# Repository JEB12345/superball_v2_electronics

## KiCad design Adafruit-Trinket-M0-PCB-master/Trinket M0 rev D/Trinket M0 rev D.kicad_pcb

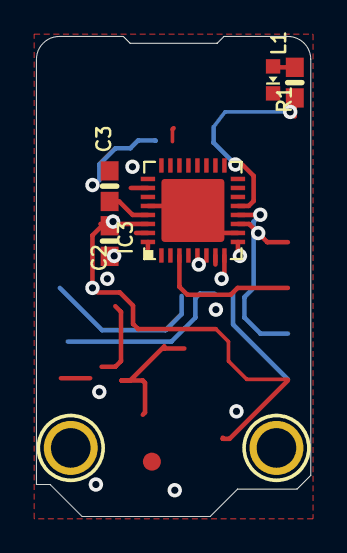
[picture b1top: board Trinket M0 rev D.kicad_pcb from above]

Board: 16 copper layers, 15.2 x 26.7 mm, 10 parts (0 on the bottom side), 7 nets.

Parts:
C2, C3: 1uF; 0603-NO
IC3: ATSAMD21E; QFN32_5MM
L1: red; CHIPLED_0603_NOOUTLINE
R1: 1.5K; 0603-NO
SWC1: TPB1,27; B1,27
SWD1: TPB1,27; B1,27
U$6: FIDUCIAL_1MM
U$8, U$9: MOUNTINGHOLE2.0; MOUNTINGHOLE_2.0_PLATED

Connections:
3.3V: C2.1, IC3.9, IC3.30
GND: C2.2, C3.2, IC3.10, IC3.28, IC3.33, L1.C
unnamed: C3.1, IC3.29
unnamed: IC3.13, R1.2
unnamed: IC3.31, SWC1.TP
unnamed: IC3.32, SWD1.TP
unnamed: L1.A, R1.1

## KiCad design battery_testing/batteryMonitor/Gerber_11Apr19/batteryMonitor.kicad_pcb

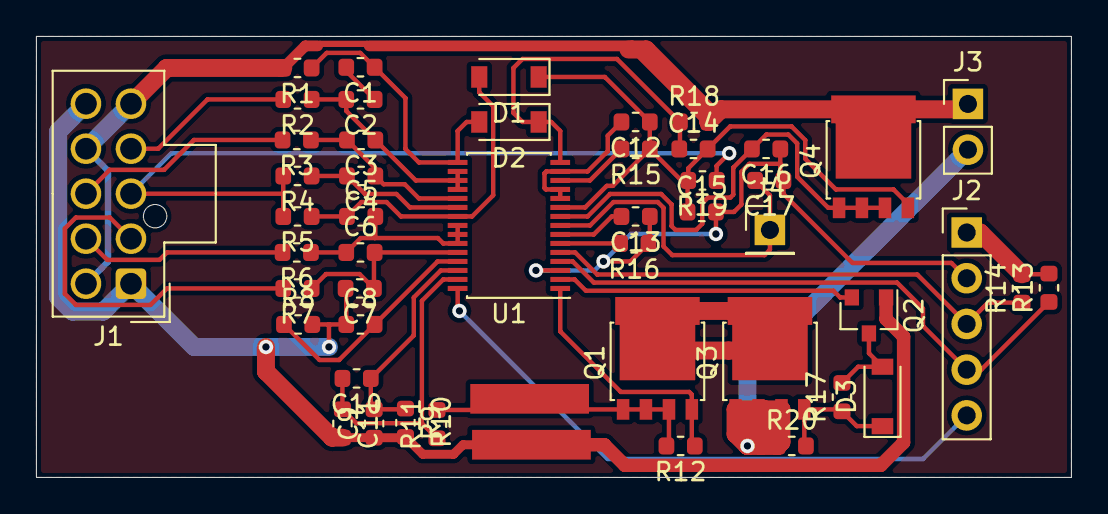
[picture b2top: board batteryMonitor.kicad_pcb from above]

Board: 2 copper layers, 57.5 x 24.5 mm, 49 parts (0 on the bottom side), 38 nets.

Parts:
C1, C2, C3, C4, C5, C6, C7, C8, C12, C13, C16: 1uF; C_0603_1608Metric
C9, C10, C11: 0.1Uf; C_0603_1608Metric
C14, C15: 10uF; C_0603_1608Metric
C17: 4.7uF; C_0603_1608Metric
D1, D2, D3: MMSD914; D_SOD-123
J1: Battery Input Connector; Molex_Nano-Fit_105310-xx10_2x05_P2.50mm_Vertical
J2: Conn_01x05_Male; PinHeader_1x05_P2.54mm_Vertical
J3: Conn_01x02_Female; PinHeader_1x02_P2.54mm_Vertical
J4: Conn_01x01_Female; PinHeader_1x01_P2.54mm_Vertical
Q1, Q3, Q4: PSMN5R8-40YS; LFPAK56
Q2: IRLML6402; SOT-23
R1, R2, R3, R4, R5, R6, R7, R8, R13, R14: 1k; R_0603_1608Metric
R9, R11, R18, R19: 100; R_0603_1608Metric
R10: 0.009; LONG_2512
R12, R17, R20: 1M; R_0603_1608Metric
R15, R16: 10k; R_0603_1608Metric
U1: BQ76930; TSSOP-30_4.4x7.8mm_P0.5mm

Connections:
/A: J1.3, R4.2, R5.2, R19.1
/Batt_GND: C7.2, C8.1, C9.1, C11.2, J1.1, J1.10, Q2.1, R8.2, R9.2, R10.1
/P1: J1.2, R7.2
/P2: J1.7, R6.2
/P4: J1.8, R3.2
/P5: J1.4, R2.2
/Pack+: J1.5, J1.6, J1.9, J3.1, Q4.5, R1.2, R18.2
/Pack-: J3.2, Q3.1, Q3.2, Q3.3, R20.1
/REGOUT: C17.2, J4.1, U1.8
/REGSRC: C16.2, Q4.1, Q4.2, Q4.3, U1.9
/Top_Batt: C14.1, D2.1, R18.1, U1.15
/VC5: C5.1, D1.2, R5.1, U1.22
/VC5x: C12.1, C14.2, C15.1, D1.1, Q4.4, R15.1, R19.2, U1.10
/alert: J2.5, U1.30
/batt_monitor_SCL: J2.3, R14.1, U1.5
/batt_monitor_SDA: J2.4, R13.1, U1.4
/external_3v3: J2.1, R13.2, R14.2
/low_GND: C13.1, C15.2, C16.1, C17.1, J2.2, R16.1, U1.3
unnamed: C1.1, D2.2, R1.1, U1.16
unnamed: C1.2, C2.1
unnamed: C2.2, C3.1, R2.1, U1.17, U1.18, U1.19
unnamed: C3.2, C4.1, R3.1, U1.20
unnamed: C4.2, R4.1, U1.21
unnamed: C5.2, C6.1, R6.1, U1.23, U1.24, U1.25
unnamed: C6.2, C7.1, R7.1, U1.26
unnamed: C8.2, R8.1, U1.27
unnamed: C9.2, C10.1, R9.1, U1.28
unnamed: C10.2, C11.1, R11.1, U1.29
unnamed: C12.2, U1.11, U1.12, U1.14
unnamed: C13.2, U1.7
unnamed: D3.1, Q3.4, R17.1, R20.2
unnamed: D3.2, Q2.3, R17.2
unnamed: Q1.1, Q1.2, Q1.3, R10.2, R11.2, R12.2
unnamed: Q1.4, R12.1, U1.1
unnamed: Q1.5, Q3.5
unnamed: Q2.2, U1.2
unnamed: R15.2, U1.13
unnamed: R16.2, U1.6

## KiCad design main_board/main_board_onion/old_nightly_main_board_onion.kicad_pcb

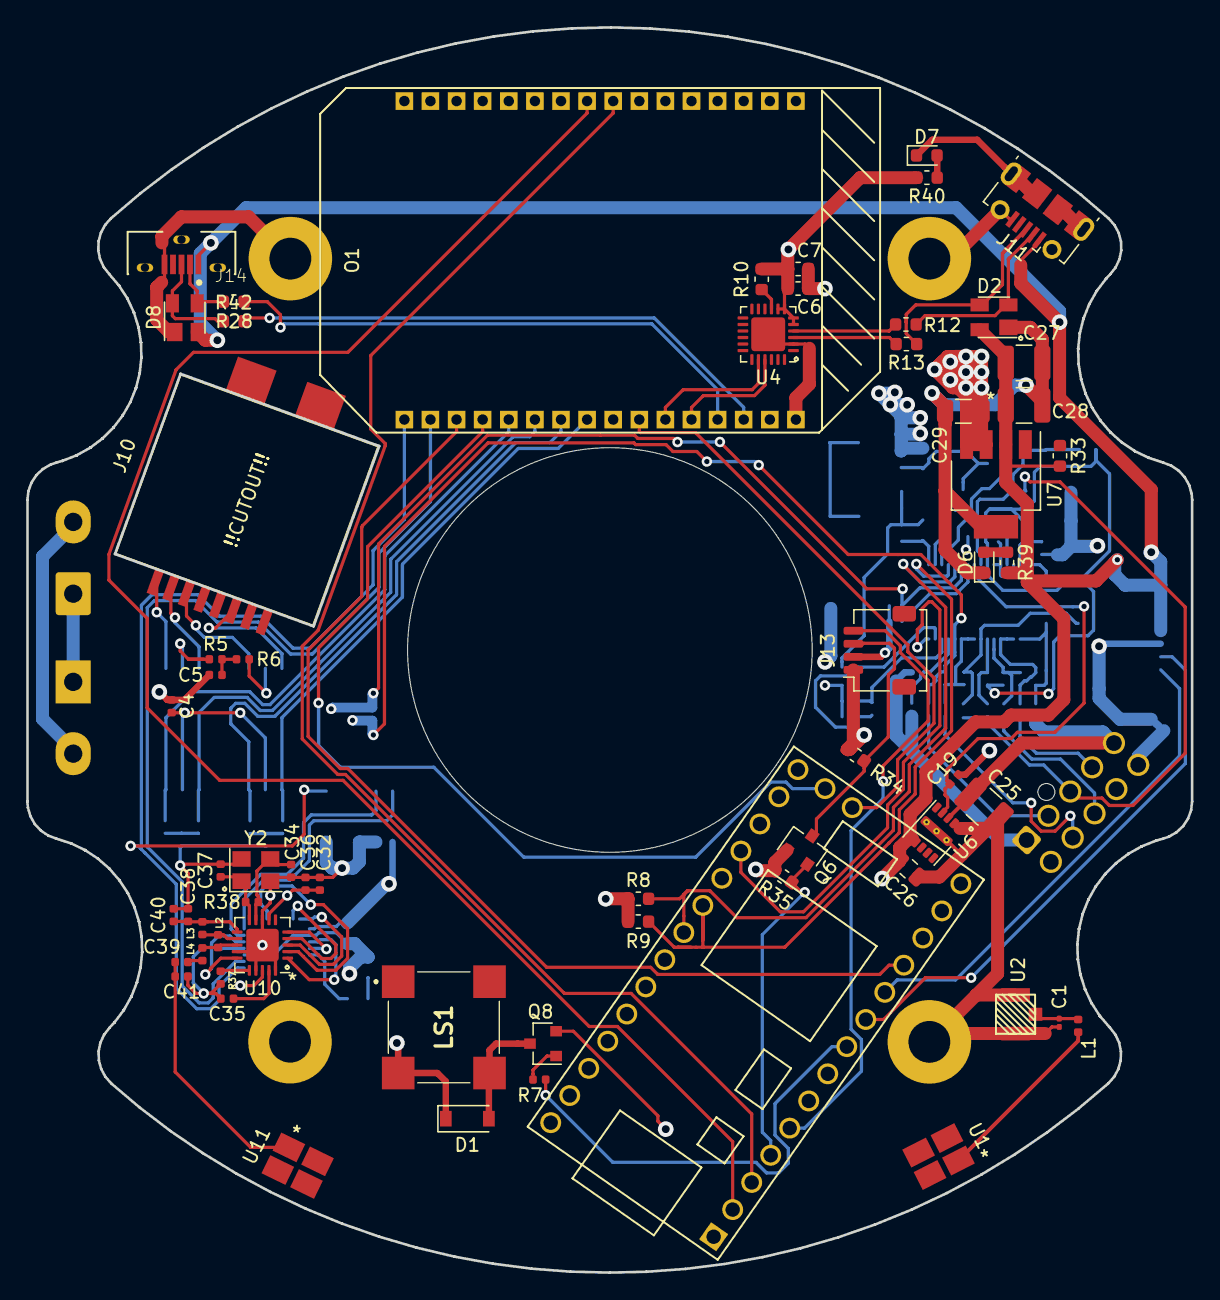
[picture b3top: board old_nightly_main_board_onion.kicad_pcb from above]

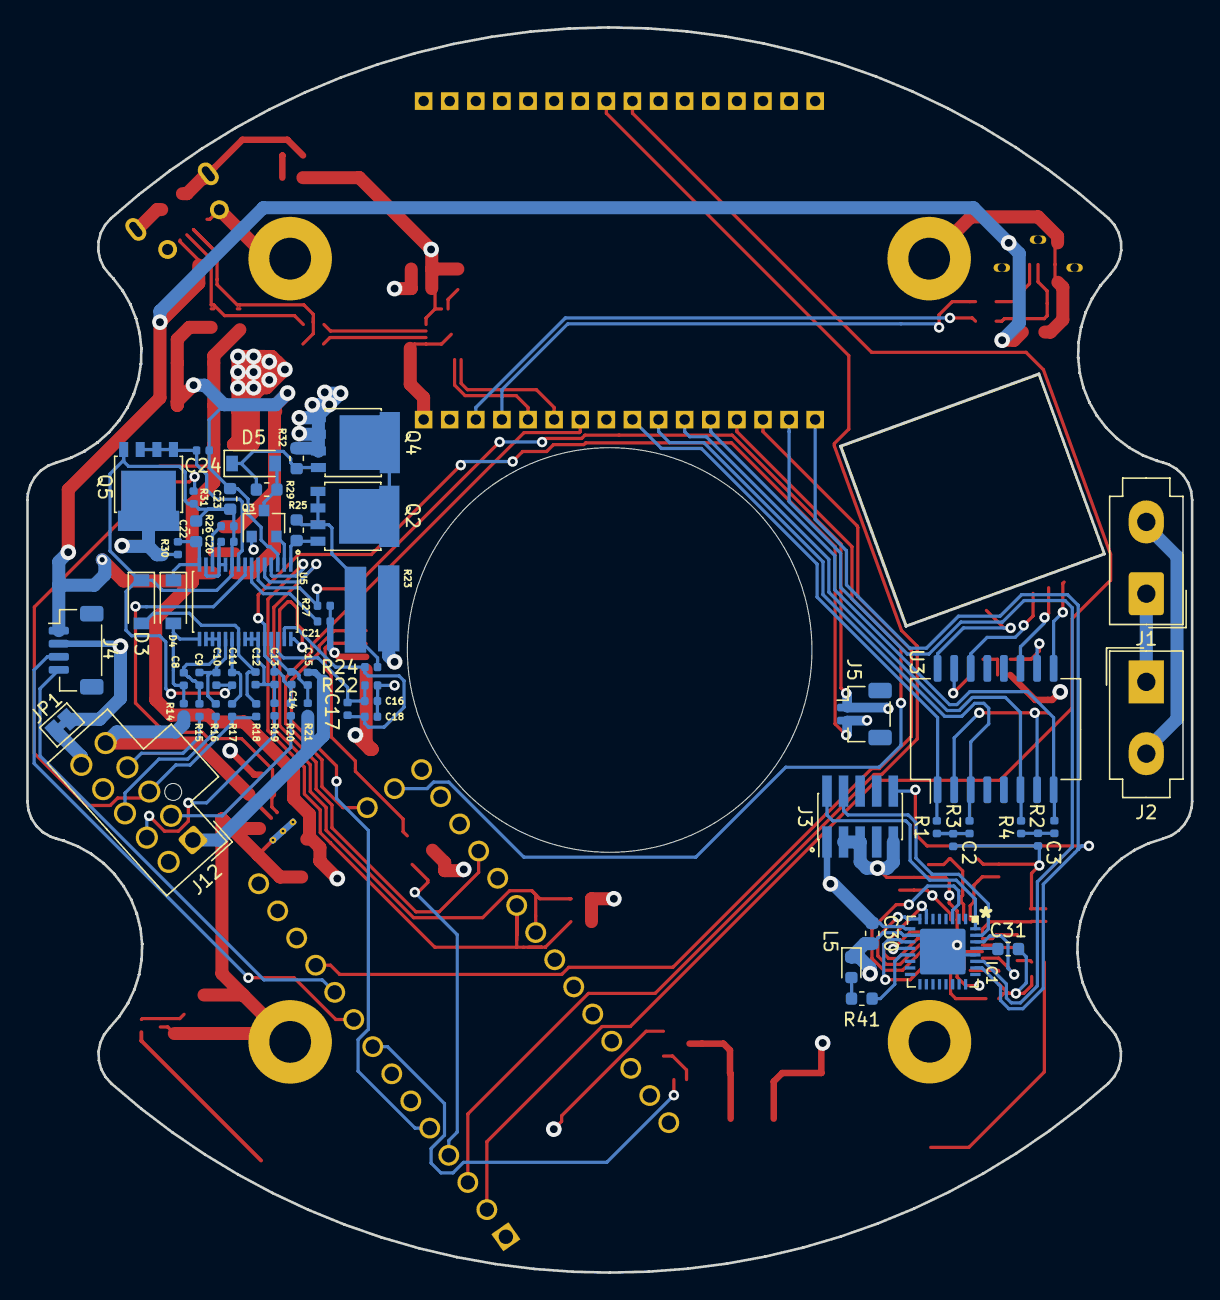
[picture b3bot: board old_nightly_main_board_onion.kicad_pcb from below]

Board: 4 copper layers, 89.2 x 95.4 mm, 128 parts (61 on the bottom side), 102 nets.

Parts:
C1: 1.3pF; C_0201_0603Metric
C2, C3: 100nF; C_0402_1005Metric
C4, C8, C9, C10, C11, C12, C13, C14, C15, C20, C21, C24: 1uF; C_0402_1005Metric
C5: 1nF/2KV; C_0402_1005Metric
C6: 0.1uF; C_0603_1608Metric
C7: 4.7uF; C_0603_1608Metric
C16, C17, C18: 0.1Uf; C_0402_1005Metric
C19: 4.7uF; C_0402_1005Metric
C22, C23: 10uF; C_0603_1608Metric
C25: C3225X7R1H106M250AC; R_1210_3225Metric
C26: 22uF; C_0805_2012Metric
C27, C28: C1210C476M9RACTU; C_1210_3225Metric
C29: TAJA336K006RNJ; C_1206_3216Metric
C30, C31: 1uF; C_0603_1608Metric
C32: 10nF; C_0402_1005Metric
C34: 1nF; C_0402_1005Metric
C35: 33nF; C_0402_1005Metric
C36, C37: 12pF; C_0402_1005Metric
C38: 2.2nF; C_0402_1005Metric
C39: 1.5pF; C_0402_1005Metric
C40: 4.7pF; C_0402_1005Metric
C41: 1.0pF; C_0402_1005Metric
D1: BAT42W-V; D_SOD-123
D2, D8: SP0503BAHT; SOT-143
D3, D4, D5: MMSD914; D_SOD-123
D6: Green; LED_0603_1608Metric
D7: Red; LED_0603_1608Metric
IC1: ATSAMD21E; QFN32_5MM
J1, J2: Hebi_Power; Molex_Mini-Fit_Jr_5566-02A_2x01_P4.20mm_Vertical
J3: Conn_02x05_Odd_Even; PinHeader_2x05_P1.27mm_Vertical_SMD
J4: SensorBoard; Molex_Pico-Clasp_501331-0407_1x04-1MP_P1.00mm_Vertical
J5: Power_On_Switch; Molex_Pico-Clasp_501331-0207_1x02-1MP_P1.00mm_Vertical
J6, J7, J8, J9: Mounting_Hole; MountingHole_3.2mm_M3_Pad
J10: RJ45; 1-338088-3
J11: USB_B_Micro_Omega; USB_Micro-B_Molex-105017-0001
J12: Battery Input Connector; Molex_Nano-Fit_105310-xx10_2x05_P2.50mm_Vertical
J13: LED_Pressure; Molex_Pico-Clasp_202396-0407_1x04-1MP_P1.00mm_Horizontal
J14: USB_B_Micro; MOLEX_105133-0001_0
JP1: SolderJumper_2_Bridged; SolderJumper-2_P1.3mm_Bridged_Pad1.0x1.5mm
L1: 1.8nH; R_0402_1005Metric
L2: 8.2nH; L_0402_1005Metric
L3: 2.7nH; L_0402_1005Metric
L4: 3.9nH; L_0402_1005Metric
L5: red; LED_0603_1608Metric
LS1: CMT-8530S-SMT-TR; CMT8530SSMTTR
O1: Omega2; Omega2p
Q2, Q4, Q5: PSMN5R8-40YS; LFPAK56
Q3: IRLML6402; SOT-23
Q6: BSS138; SOT-23
Q8: MMBT3904; SOT-23
R1, R2, R3, R4: 49.9; R_0402_1005Metric
R5, R6: 75; R_0402_1005Metric
R7, R22, R24, R30, R31: 100; R_0402_1005Metric
R8, R9, R33: 10k; R_0603_1608Metric
R10, R39, R40, R41: 1k; R_0603_1608Metric
R12, R13, R28, R42: 33; R_0603_1608Metric
R14, R15, R16, R17, R18, R19, R20, R21: 1k; R_0402_1005Metric
R23: 0.009; LONG_2512
R25, R29, R32: 1M; R_0603_1608Metric
R26, R27: 10k; R_0402_1005Metric
R34, R35: 10K; R_0603_1608Metric
R37: 22k; R_0402_1005Metric
R38: 1M; R_0402_1005Metric
U1, U11: molex_antenna_47948-0001; Molex_47948-0001
U2: conn_smt; U.FL-R-SMT-1(01)
U3: H1102; SOIC-16W_7.5x12.8mm_P1.27mm
U4: CP2102N-A01-GQFN24; QFN-24-1EP_4x4mm_P0.5mm_EP2.6x2.6mm
U5: BQ76930; TSSOP-30_4.4x7.8mm_P0.5mm
U6: LMZM23601V5; Texas_SIL0010A_MicroSiP-10-1EP_3.8x3mm_P0.6mm_EP0.7x2.9mm_T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
U7: lp3965v3; SOT-223-5
U8: Teensy-LC; Teensy_LC_Min
U10: nRF24L01P; QFN-20-1EP_4x4mm_P0.5mm_EP2.5x2.5mm
Y2: CX3225SB16000H0FLJCC; Crystal_SMD_3225-4Pin_3.2x2.5mm

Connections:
+3V3: C6.1, C7.1, C29.1, C30.1, C32.1, C34.1, D1.1, IC1.9, IC1.30, J3.1, LS1.2, O1.B2, Q6.1, R8.1, R9.1, R10.1, R35.1, R40.2, U4.5, U4.6, U4.7, U4.8, U7.3, U7.4, U10.7, U10.15, U10.18
+5V: C26.2, C27.1, C28.1, D2.4, D8.2, J4.1, J11.1, J13.1, J14.1, R33.2, R34.1, R39.2, U6.6, U6.7, U7.2, U8.33
/Button_L: J5.1, R27.2, U5.6
/Button_R: C13.2, C14.1, J5.2, R20.1, U5.26
/I2C_SCL: R8.2, U5.5, U8.26
/I2C_SDA: R9.2, U5.4, U8.25
/LED_Strip_CMD: J13.3, Q6.3, R34.2
/Omega2/D+IN_Omega: D2.3, J11.3, R13.1
/Omega2/D+_Omega: R13.2, U4.3
/Omega2/D-IN_Omega: D2.2, J11.2, R12.1
/Omega2/D-_Omega: R12.2, U4.4
/Omega2/PC_RXD: O1.B6, U4.20
/Omega2/PC_TXD: O1.B5, U4.21
/Omega2/RX+: O1.B12, R2.2, U3.8
/Omega2/RX-: O1.B11, R4.2, U3.6
/Omega2/TX+: O1.B10, R3.2, U3.3
/Omega2/TX-: O1.B9, R1.2, U3.1
/Omega2/extra_USB+: O1.B3, R42.2
/Omega2/extra_USB-: O1.B4, R28.2
/Omega2/extra_in_USB+: D8.4, J14.3, R42.1
/Omega2/extra_in_USB-: D8.3, J14.2, R28.1
/Operational_Sig: IC1.27, O1.B15
/Pack+: C25.1, J1.2, J2.2, J12.5, J12.6, J12.9, Q5.5, R14.2, R30.2, U6.3
/Pack_GND: J1.1, J2.1, Q4.1, Q4.2, Q4.3, R32.1
/Pressure_Sensor: J13.4, U8.5
/REGOUT: C19.2, U5.8, U6.4
/SensorBoard_RX: J4.3, U8.9
/SensorBoard_TX: J4.4, U8.10
/Teensy/LED_Strip_Lighting: Q6.2, R35.2, U8.4
/Teensy/buzzer: R7.2, U8.8
/Teensy_Program: O1.B7, U8.18
/Teensy_RX: O1.A9, U8.2
/Teensy_Ready: O1.B14, U8.11
/Teensy_TX: O1.A8, U8.3
/batteryMonitor/A: J12.3, R17.2, R18.2, R31.1
/batteryMonitor/Batt_GND: C15.2, C16.1, C18.2, J12.1, J12.10, JP1.1, Q3.1, R21.2, R22.2, R23.1
/batteryMonitor/P1: J12.2, R20.2
/batteryMonitor/P2: J12.7, R19.2
/batteryMonitor/P4: J12.8, R16.2
/batteryMonitor/P5: J12.4, R15.2
/batteryMonitor/REGSRC: C24.2, Q5.1, Q5.2, Q5.3, U5.9
/batteryMonitor/Top_Batt: C22.1, D4.1, R30.1, U5.15
/batteryMonitor/VC5: C12.1, D3.2, R18.1, U5.22
/batteryMonitor/VC5x: C10.2, C11.1, C20.1, C22.2, C23.1, D3.1, Q5.4, R26.1, R31.2, U5.10
/bq76930_Alert: U5.30, U8.23
/mRF_MOSI: IC1.7, U10.4
/nRF24L01+Trinket/Trinket_M0_rev_D/SWCLK: IC1.31, J3.4
/nRF24L01+Trinket/Trinket_M0_rev_D/SWDIO: IC1.32, J3.2
/nRF_CE: IC1.11, U10.1
/nRF_CSN: IC1.3, U10.2
/nRF_MISO: IC1.12, U10.5
/nRF_SCK: IC1.8, U10.3
/~M0_RESET: IC1.26, J3.10, O1.B16
/~Reset_Teensy: O1.B13, U8.19
GND: C1.2, C2.2, C3.2, C4.1, C5.1, C6.2, C7.2, C19.1, C21.1, C23.2, C24.1, C25.2, C26.1, C27.2, C28.2, C29.2, C30.2, C31.2, C32.2, C34.2, C35.2, C36.2, C37.2, C38.2, C40.2, C41.1, D2.1, D6.1, D7.1, D8.1, IC1.10, IC1.28, IC1.33, J3.3, J3.5, J3.9, J4.2, J6.1, J7.1, J8.1, J9.1, J11.5, J11.6, J13.2, J14.5, J14.6, JP1.2, L5.1, O1.A1, O1.B1, Q8.2, R27.1, R37.2, U2.1, U2.2, U4.2, U4.25, U5.3, U6.1, U6.2, U6.11, U7.5, U8.1, U8.32, U10.8, U10.14, U10.17, U10.20, U10.21, Y2.2, Y2.4
unnamed: C1.1, L1.1, U2.3
unnamed: C2.1, R1.1, R3.1
unnamed: C3.1, R2.1, R4.1
unnamed: C4.2, U3.2, U3.7
unnamed: C5.2, R5.2, R6.2
unnamed: C8.1, D4.2, R14.1, U5.16
unnamed: C8.2, C9.1, R15.1, U5.17, U5.18, U5.19
unnamed: C9.2, C10.1, R16.1, U5.20
unnamed: C11.2, R17.1, U5.21
unnamed: C12.2, C13.1, R19.1, U5.23, U5.24, U5.25
unnamed: C14.2, C15.1, R21.1, U5.27
unnamed: C16.2, C17.1, R22.1, U5.28
unnamed: C17.2, C18.1, R24.1, U5.29
unnamed: C20.2, U5.11, U5.12, U5.14
unnamed: C21.2, U5.7
unnamed: C31.1, IC1.29
unnamed: C35.1, U10.19
unnamed: C36.1, R38.1, U10.9, Y2.3
unnamed: C37.1, R38.2, U10.10, Y2.1
unnamed: C38.1, C40.1, L3.1, U10.11
unnamed: C39.1, C41.2, U11.1
unnamed: C39.2, L4.1
unnamed: D1.2, LS1.3, Q8.3
unnamed: D5.1, Q4.4, R29.1, R32.2
unnamed: D5.2, Q3.3, R29.2
unnamed: D6.2, R39.1
unnamed: D7.2, R40.1
unnamed: IC1.13, R41.2
unnamed: J10.1, U3.9
unnamed: J10.2, U3.11
unnamed: J10.3, U3.14
unnamed: J10.6, U3.16
unnamed: L1.2, U1.1
unnamed: L2.1, L3.2, U10.12
unnamed: L2.2, L4.2, U10.13
unnamed: L5.2, R41.1
unnamed: Q2.1, Q2.2, Q2.3, R23.2, R24.2, R25.2
unnamed: Q2.4, R25.1, U5.1
unnamed: Q2.5, Q4.5
unnamed: Q3.2, U5.2
unnamed: Q8.1, R7.1
unnamed: R5.1, U3.10
unnamed: R6.1, U3.15
unnamed: R10.2, U4.9
unnamed: R26.2, U5.13
unnamed: R33.1, U7.1
unnamed: R37.1, U10.16

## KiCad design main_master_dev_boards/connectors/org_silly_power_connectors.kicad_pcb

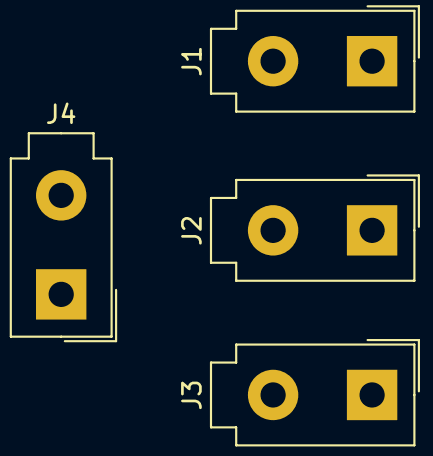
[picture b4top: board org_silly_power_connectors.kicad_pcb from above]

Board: 2 copper layers, 4 parts (0 on the bottom side), 2 nets, no tracks yet.

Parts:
J1, J2, J3, J4: vert_miniFit_jr; Molex_MiniFit-JR-5556-02A_2x01x4.20mm_Straight

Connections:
unnamed: J1.1, J2.1, J3.1, J4.1
unnamed: J1.2, J2.2, J3.2, J4.2
